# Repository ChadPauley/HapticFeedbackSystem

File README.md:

The purpose of this directory is to store PCB work and documentation on my first PCB design that was developed and sent to a fab house. While working on a team, I was tasked with designing the PCB layout for a Carrier Board that houses a CM4 module.
There are three versions of the PCB as we discovered issues and misleading information in the CM4 documentation such as camera pin layout. The final version worked and is in the primary CAD and schematic directory.

Version 2:
I2C lines for CAM1 are used for CAM0 which makes the camera a little finicky.

Version 3:
V3 fixes the issue with the camera and acts as a more ideal PCB.
--------------------------------------------------------------------------

After this project I have begun to focus more on the KiCAD software to design PCB fabs as a hobby due to the limitations of EAGLE only allowing 2 layers for the free version.

--------------------------------------------------------------------------
Real Fab Shape/Size:

--------------------------------------------------------------------------
CAD Layout:

--------------------------------------------------------------------------
Net paths:

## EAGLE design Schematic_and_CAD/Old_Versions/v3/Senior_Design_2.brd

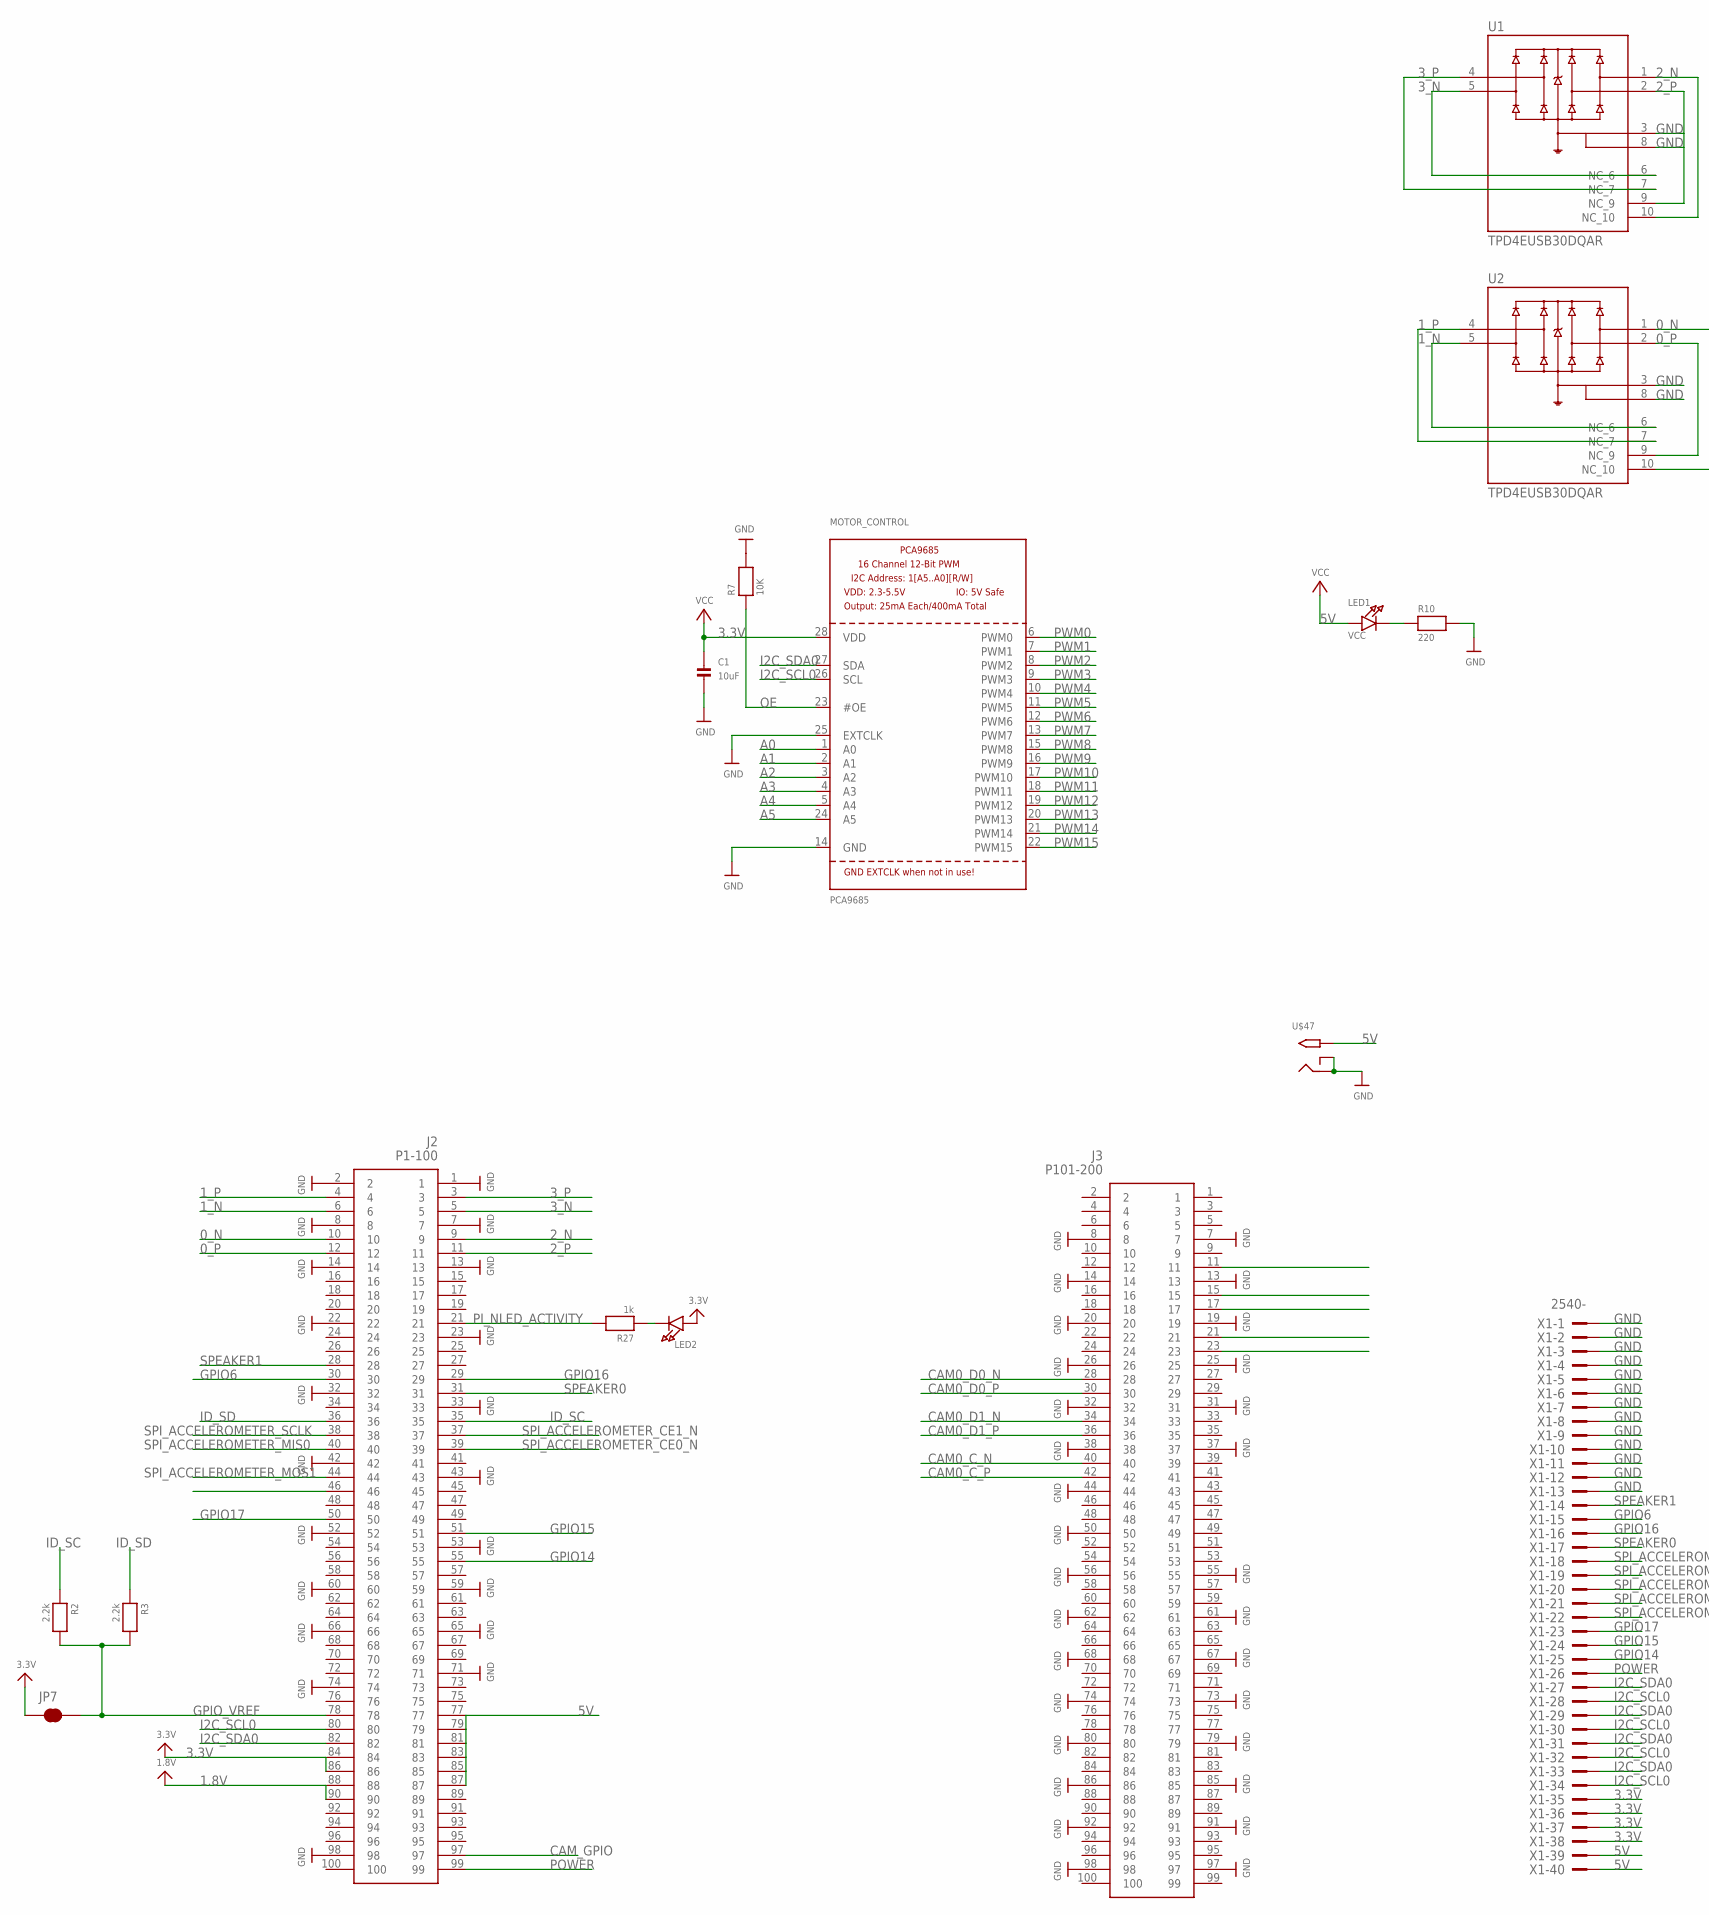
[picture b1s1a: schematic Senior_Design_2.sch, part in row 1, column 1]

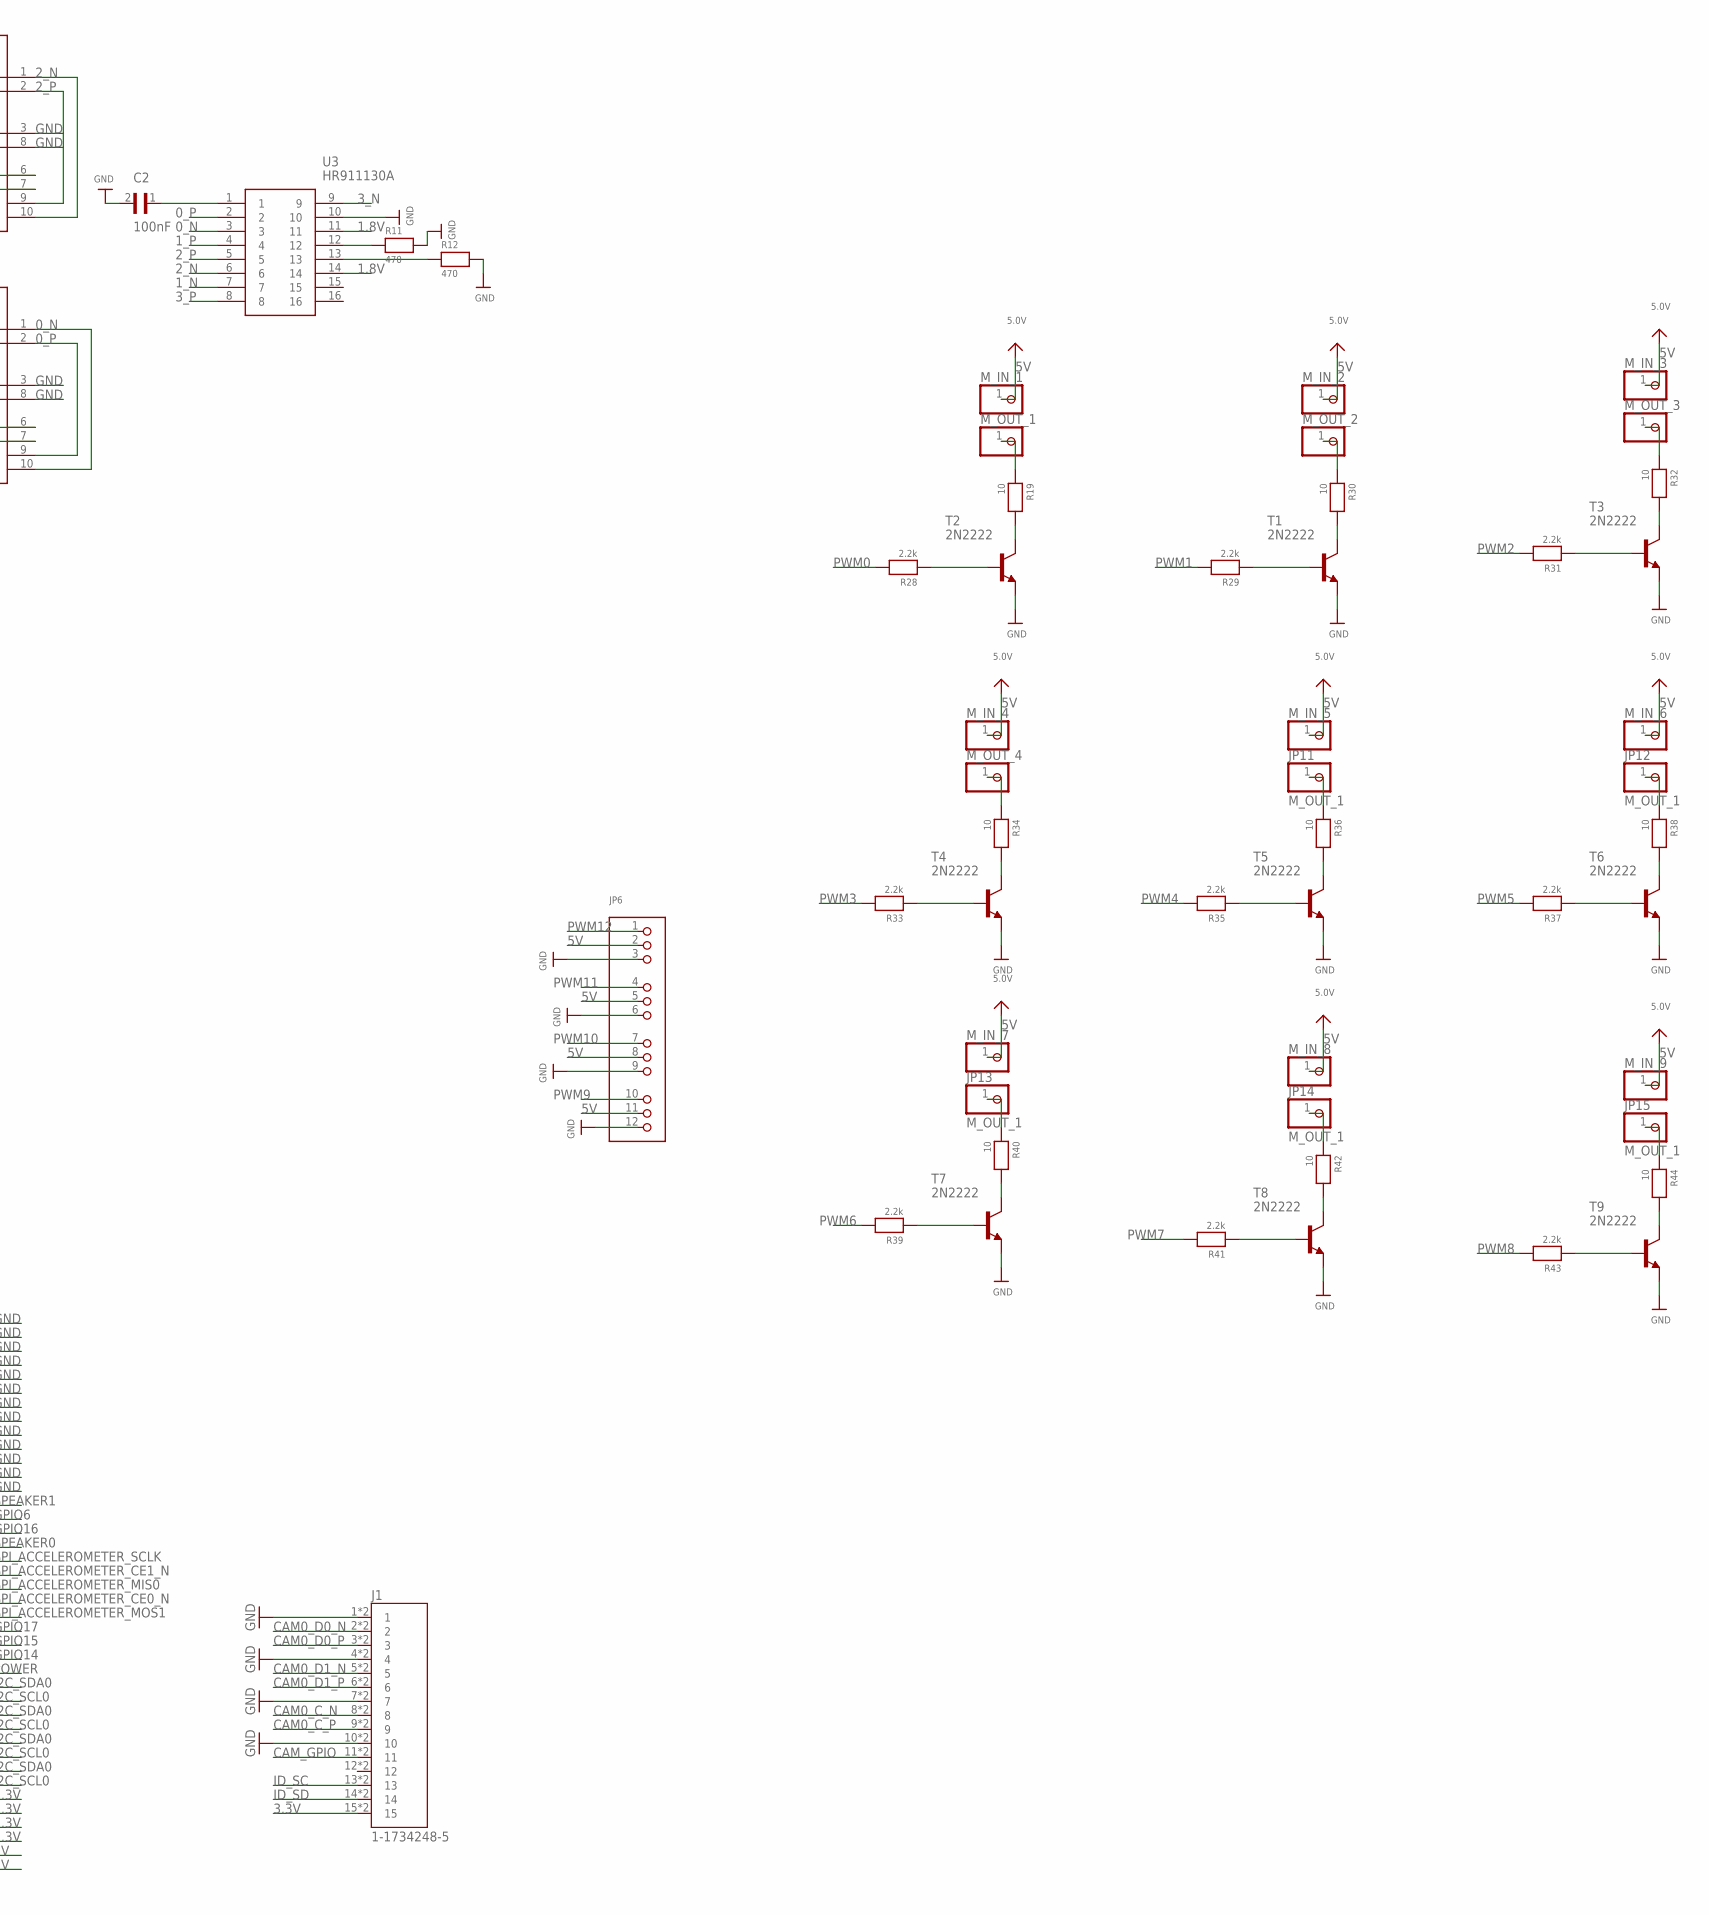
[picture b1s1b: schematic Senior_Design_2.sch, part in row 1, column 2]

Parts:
C1: 10uF; 0805@1
C2: 100nF; CAPC1608X90
J1: 1-1734248-5; TE_1-1734248-5
J2: P1-100; DF40C100DS04V51; MPN MCW0406MD1003BP100
J3: P101-200; DF40C100DS04V51
JP6: HEADER-3X04; 3X04
JP7: JUMPER-SMT_2_NC_TRACE_NO-SILK; SMT-JUMPER_2_NC_TRACE_NO-SILK
JP11, JP12, JP13, JP14, JP15: M_OUT_1; 1X01
LED1: VCC; CHIPLED_0805
LED2: LED0603; CHIPLED_0603; MPN LS Q976-NR-1
MOTOR_CONTROL: PCA9685; TSSOP28
M_IN_1, M_IN_2, M_IN_3, M_IN_4, M_IN_5, M_IN_6, M_IN_7, M_IN_8, M_IN_9: PINHD-1X1; 1X01
M_OUT_1, M_OUT_2, M_OUT_3, M_OUT_4: PINHD-1X1; 1X01
R2, R3, R28, R29, R31, R33, R35, R37, R39, R41, R43: 2.2k; 0805
R7: 10K; 0805
R10: 220; 0805
R11, R12: 470; 0805
R19, R30, R32, R34, R36, R38, R40, R42, R44: 10; 0805
R27: 1k; 0805
T1, T2, T3, T4, T5, T6, T7, T8, T9: 2N2222; TO92-EBC-OVAL
U1, U2: TPD4EUSB30DQAR; IC_TPD4EUSB30DQAR
U3: HR911130A
U$47: 2.1MMJACKTHM; PJ-102A
X1: 2540-; PAK100/2500-40

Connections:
0_N: J2.10, U2.1 (D1+), U2.10 (NC_10), U3.3
0_P: J2.12, U2.2 (D1-), U2.9 (NC_9), U3.2
1.8V: J2.88, J2.90, U3.11, U3.14
1_N: J2.6, U2.5 (D2-), U2.6 (NC_6), U3.7
1_P: J2.4, U2.4 (D2+), U2.7 (NC_7), U3.4
2_N: J2.9, U1.1 (D1+), U1.10 (NC_10), U3.6
2_P: J2.11, U1.2 (D1-), U1.9 (NC_9), U3.5
3.3V: C1.1, J1.15, J1.15_1 (15), J2.84, J2.86, JP7.1, LED2.A, MOTOR_CONTROL.28 (VDD), X1.35, X1.36, X1.37, X1.38
3_N: J2.5, U1.5 (D2-), U1.6 (NC_6), U3.9
3_P: J2.3, U1.4 (D2+), U1.7 (NC_7), U3.8
5V: J2.77, J2.79, J2.81, J2.83, J2.85, J2.87, JP6.2, JP6.5, JP6.8, JP6.11, LED1.A, M_IN_1.1, M_IN_2.1, M_IN_3.1, M_IN_4.1, M_IN_5.1, M_IN_6.1, M_IN_7.1, M_IN_8.1, M_IN_9.1, U$47.TIP, X1.39, X1.40
A0: MOTOR_CONTROL.1 (A0)
A1: MOTOR_CONTROL.2 (A1)
A2: MOTOR_CONTROL.3 (A2)
A3: MOTOR_CONTROL.4 (A3)
A4: MOTOR_CONTROL.5 (A4)
A5: MOTOR_CONTROL.24 (A5)
CAM0_C_N: J1.8, J1.8_1 (8), J3.40
CAM0_C_P: J1.9, J1.9_1 (9), J3.42
CAM0_D0_N: J1.2, J1.2_1 (2), J3.28
CAM0_D0_P: J1.3, J1.3_1 (3), J3.30
CAM0_D1_N: J1.5, J1.5_1 (5), J3.34
CAM0_D1_P: J1.6, J1.6_1 (6), J3.36
CAM_GPIO: J1.11, J1.11_1 (11), J2.97
GND: C1.2, C2.2, J1.1, J1.1_1 (1), J1.4, J1.4_1 (4), J1.7, J1.7_1 (7), J1.10, J1.10_1 (10), J2.1, J2.2, J2.7, J2.8, J2.13, J2.14, J2.22, J2.23, J2.32, J2.33, J2.42, J2.43, J2.52, J2.53, J2.59, J2.60, J2.65, J2.66, J2.71, J2.74, J2.98, J3.7, J3.8, J3.13, J3.14, J3.19, J3.20, J3.25, J3.26, J3.31, J3.32, J3.37, J3.38, J3.44, J3.50, J3.55, J3.56, J3.61, J3.62, J3.67, J3.68, J3.73, J3.74, J3.79, J3.80, J3.85, J3.86, J3.91, J3.92, J3.97, J3.98, JP6.3, JP6.6, JP6.9, JP6.12, MOTOR_CONTROL.14 (GND), MOTOR_CONTROL.25 (EXTCLK), R7.2, R10.2, R11.2, R12.2, T1.E, T2.E, T3.E, T4.E, T5.E, T6.E, T7.E, T8.E, T9.E, U1.3 (GND_3), U1.8 (GND_8), U2.3 (GND_3), U2.8 (GND_8), U3.10, U$47.RING, U$47.RING_SW, X1.1, X1.2, X1.3, X1.4, X1.5, X1.6, X1.7, X1.8, X1.9, X1.10, X1.11, X1.12, X1.13
GPIO6: J2.30, X1.15
GPIO14: J2.55, X1.25
GPIO15: J2.51, X1.24
GPIO16: J2.29, X1.16
GPIO17: J2.50, X1.23
GPIO_VREF: J2.78, JP7.2, R2.2, R3.2
I2C_SCL0: J2.80, MOTOR_CONTROL.26 (SCL), X1.28, X1.30, X1.32, X1.34
I2C_SDA0: J2.82, MOTOR_CONTROL.27 (SDA), X1.27, X1.29, X1.31, X1.33
ID_SC: J1.13, J1.13_1 (13), J2.35, R2.1
ID_SD: J1.14, J1.14_1 (14), J2.36, R3.1
unnamed: LED1.C, R10.1
unnamed: C2.1, U3.1
unnamed: R11.1, U3.12
unnamed: R12.1, U3.13
unnamed: R19.2, T2.C
unnamed: LED2.C, R27.1
unnamed: R28.1, T2.B
unnamed: M_OUT_1.1, R19.1
unnamed: R29.1, T1.B
unnamed: R30.2, T1.C
unnamed: M_OUT_2.1, R30.1
unnamed: R31.1, T3.B
unnamed: R32.2, T3.C
unnamed: M_OUT_3.1, R32.1
unnamed: R33.1, T4.B
unnamed: R34.2, T4.C
unnamed: M_OUT_4.1, R34.1
unnamed: R35.1, T5.B
unnamed: R36.2, T5.C
unnamed: JP11.1, R36.1
unnamed: R37.1, T6.B
unnamed: R38.2, T6.C
unnamed: JP12.1, R38.1
unnamed: R39.1, T7.B
unnamed: R40.2, T7.C
unnamed: JP13.1, R40.1
unnamed: R41.1, T8.B
unnamed: R42.2, T8.C
unnamed: JP14.1, R42.1
unnamed: R43.1, T9.B
unnamed: R44.2, T9.C
unnamed: JP15.1, R44.1
OE: MOTOR_CONTROL.23 (#OE), R7.1
PI_NLED_ACTIVITY: J2.21, R27.2
POWER: J2.99, X1.26
PWM0: MOTOR_CONTROL.6 (PWM0), R28.2
PWM1: MOTOR_CONTROL.7 (PWM1), R29.2
PWM2: MOTOR_CONTROL.8 (PWM2), R31.2
PWM3: MOTOR_CONTROL.9 (PWM3), R33.2
PWM4: MOTOR_CONTROL.10 (PWM4), R35.2
PWM5: MOTOR_CONTROL.11 (PWM5), R37.2
PWM6: MOTOR_CONTROL.12 (PWM6), R39.2
PWM7: MOTOR_CONTROL.13 (PWM7), R41.2
PWM8: MOTOR_CONTROL.15 (PWM8), R43.2
PWM9: JP6.10, MOTOR_CONTROL.16 (PWM9)
PWM10: JP6.7, MOTOR_CONTROL.17 (PWM10)
PWM11: JP6.4, MOTOR_CONTROL.18 (PWM11)
PWM12: JP6.1, MOTOR_CONTROL.19 (PWM12)
PWM13: MOTOR_CONTROL.20 (PWM13)
PWM14: MOTOR_CONTROL.21 (PWM14)
PWM15: MOTOR_CONTROL.22 (PWM15)
SPEAKER0: J2.31, X1.17
SPEAKER1: J2.28, X1.14
SPI_ACCELEROMETER_CE0_N: J2.39, X1.21
SPI_ACCELEROMETER_CE1_N: J2.37, X1.19
SPI_ACCELEROMETER_MIS0: J2.40, X1.20
SPI_ACCELEROMETER_MOS1: J2.44, X1.22
SPI_ACCELEROMETER_SCLK: J2.38, X1.18

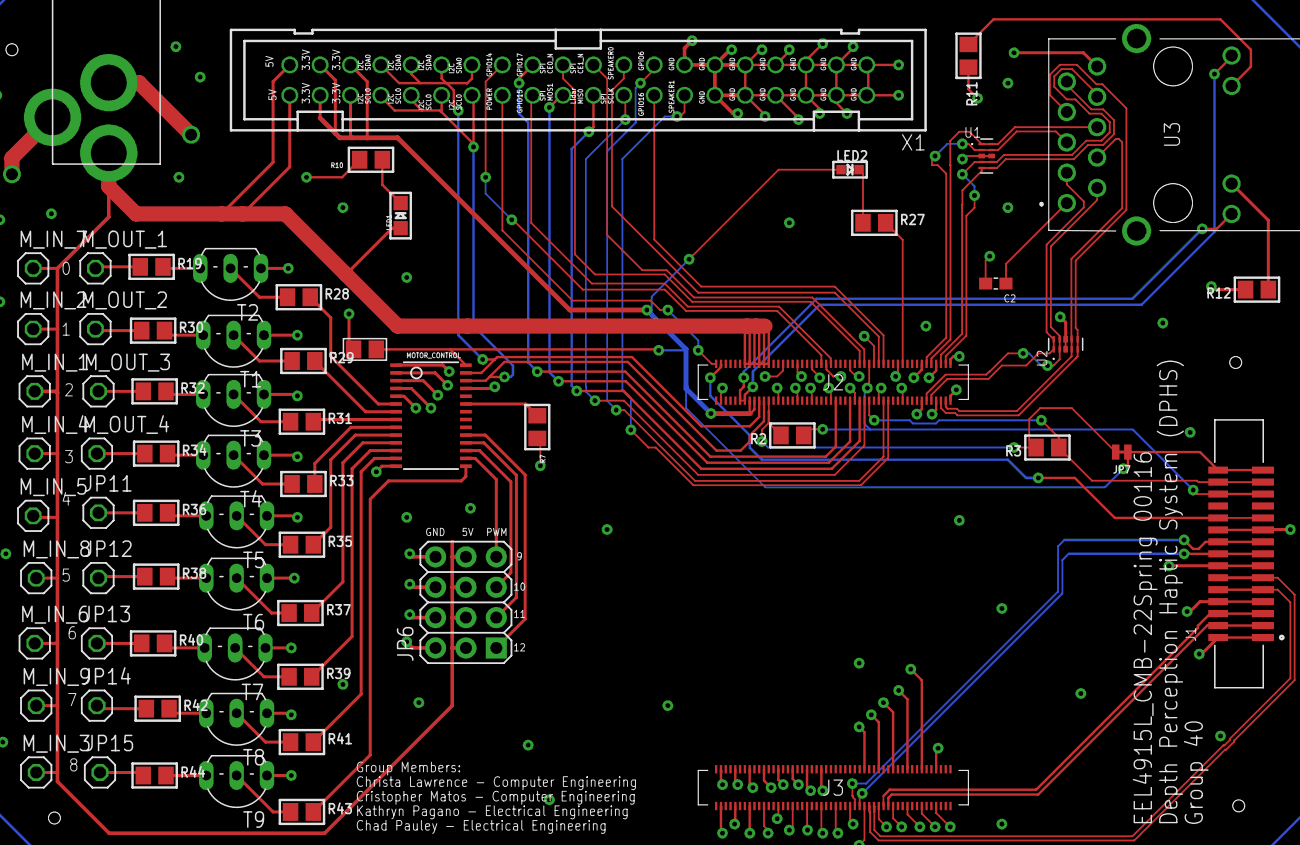
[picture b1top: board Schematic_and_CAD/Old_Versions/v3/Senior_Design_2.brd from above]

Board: 2 copper layers, 67 parts (0 on the bottom side), 84 nets.

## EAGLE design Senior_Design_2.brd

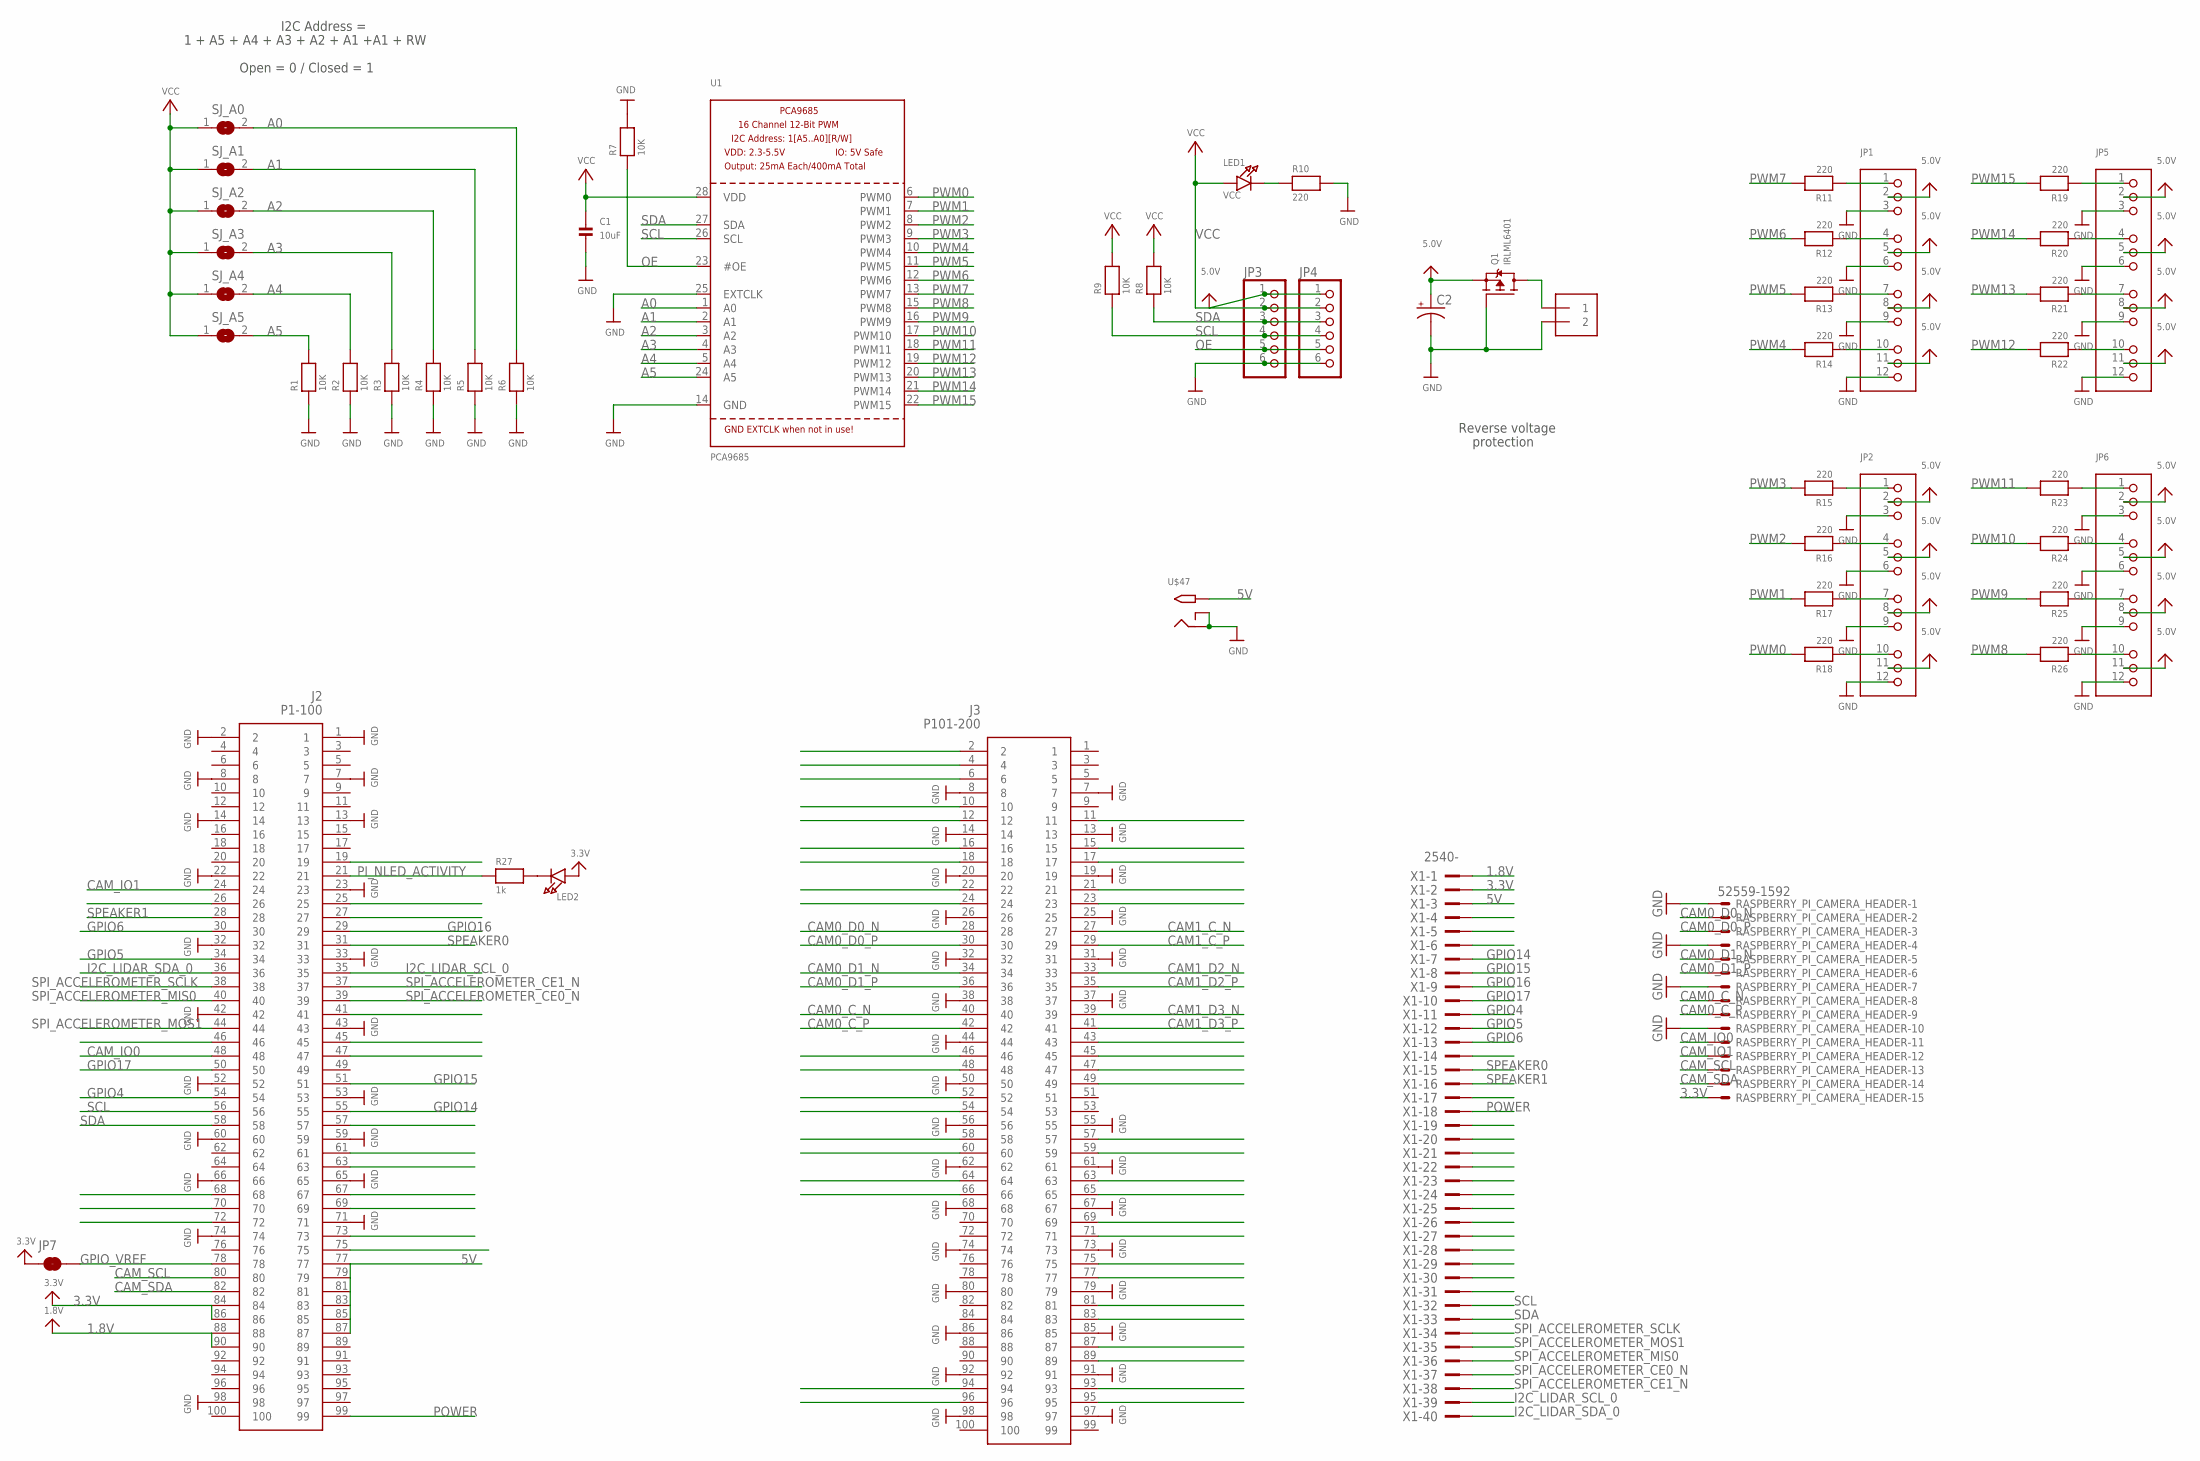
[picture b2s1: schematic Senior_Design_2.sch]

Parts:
C1: 10uF; 0805@1
C2: CPOL-USE3.5-8; E3,5-8
J1: TERMBLOCK_1X2-3.5MM; 1X2-3.5MM
J2: P1-100; DF40C100DS04V51; MPN MCW0406MD1003BP100
J3: P101-200; DF40C100DS04V51
JP1, JP2, JP5, JP6: HEADER-3X04; 3X04
JP3, JP4: PINHD-1X6CB; 1X06-CLEANBIG
JP7: JUMPER-SMT_2_NC_TRACE_NO-SILK; SMT-JUMPER_2_NC_TRACE_NO-SILK
LED1: VCC; CHIPLED_0805
LED2: LED0603; CHIPLED_0603; MPN LS Q976-NR-1
Q1: IRLML6401; SOT23-WIDE
R1, R2, R3, R4, R5, R6, R7, R8, R9: 10K; 0805
R10, R11, R12, R13, R14, R15, R16, R17, R18, R19, R20, R21, R22, R23, R24, R25, R26: 220; 0805
R27: 1k; _0402MP; MPN ERJ-8ENF1001V
RASPBERRY_PI_CAMERA_HEADER: 52559-1592
SJ_A0, SJ_A1, SJ_A2, SJ_A3, SJ_A4, SJ_A5: SOLDERJUMPERREFLOW_NOPASTE; SOLDERJUMPER_REFLOW_NOPASTE
U1: PCA9685; TSSOP28
U$47: 2.1MMJACKTHM; PJ-102A
X1: 2540-; PAK100/2500-40

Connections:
1.8V: J2.88, J2.90, X1.1
3.3V: J2.84, J2.86, JP7.1, LED2.A, RASPBERRY_PI_CAMERA_HEADER.15, X1.2
5.0V: C2.+, JP1.2, JP1.5, JP1.8, JP1.11, JP2.2, JP2.5, JP2.8, JP2.11, JP3.1, JP4.1, JP5.2, JP5.5, JP5.8, JP5.11, JP6.2, JP6.5, JP6.8, JP6.11, Q1.2 (S)
5V: J2.77, J2.79, J2.81, J2.83, J2.85, J2.87, U$47.TIP, X1.3
A0: R6.2, SJ_A0.2, U1.1 (A0)
A1: R5.2, SJ_A1.2, U1.2 (A1)
A2: R4.2, SJ_A2.2, U1.3 (A2)
A3: R3.2, SJ_A3.2, U1.4 (A3)
A4: R2.2, SJ_A4.2, U1.5 (A4)
A5: R1.2, SJ_A5.2, U1.24 (A5)
CAM0_C_N: J3.40, RASPBERRY_PI_CAMERA_HEADER.8
CAM0_C_P: J3.42, RASPBERRY_PI_CAMERA_HEADER.9
CAM0_D0_N: J3.28, RASPBERRY_PI_CAMERA_HEADER.2
CAM0_D0_P: J3.30, RASPBERRY_PI_CAMERA_HEADER.3
CAM0_D1_N: J3.34, RASPBERRY_PI_CAMERA_HEADER.5
CAM0_D1_P: J3.36, RASPBERRY_PI_CAMERA_HEADER.6
CAM1_C_N: J3.27
CAM1_C_P: J3.29
CAM1_D2_N: J3.33
CAM1_D2_P: J3.35
CAM1_D3_N: J3.39
CAM1_D3_P: J3.41
CAM_IO0: J2.48, RASPBERRY_PI_CAMERA_HEADER.11
CAM_IO1: J2.24, RASPBERRY_PI_CAMERA_HEADER.12
CAM_SCL: J2.80, RASPBERRY_PI_CAMERA_HEADER.13
CAM_SDA: J2.82, RASPBERRY_PI_CAMERA_HEADER.14
GND: C1.2, C2.-, J1.2, J2.1, J2.2, J2.7, J2.8, J2.13, J2.14, J2.22, J2.23, J2.32, J2.33, J2.42, J2.43, J2.52, J2.53, J2.59, J2.60, J2.65, J2.66, J2.71, J2.74, J2.98, J3.7, J3.8, J3.13, J3.14, J3.19, J3.20, J3.25, J3.26, J3.31, J3.32, J3.37, J3.38, J3.44, J3.50, J3.55, J3.56, J3.61, J3.62, J3.67, J3.68, J3.73, J3.74, J3.79, J3.80, J3.85, J3.86, J3.91, J3.92, J3.97, J3.98, JP1.3, JP1.6, JP1.9, JP1.12, JP2.3, JP2.6, JP2.9, JP2.12, JP3.6, JP4.6, JP5.3, JP5.6, JP5.9, JP5.12, JP6.3, JP6.6, JP6.9, JP6.12, Q1.1 (G), R1.1, R2.1, R3.1, R4.1, R5.1, R6.1, R7.2, R10.2, RASPBERRY_PI_CAMERA_HEADER.1, RASPBERRY_PI_CAMERA_HEADER.4, RASPBERRY_PI_CAMERA_HEADER.7, RASPBERRY_PI_CAMERA_HEADER.10, U1.14 (GND), U1.25 (EXTCLK), U$47.RING, U$47.RING_SW
GPIO4: J2.54, X1.11
GPIO5: J2.34, X1.12
GPIO6: J2.30, X1.13
GPIO14: J2.55, X1.7
GPIO15: J2.51, X1.8
GPIO16: J2.29, X1.9
GPIO17: J2.50, X1.10
GPIO_VREF: J2.78, JP7.2
I2C_LIDAR_SCL_0: J2.35, X1.39
I2C_LIDAR_SDA_0: J2.36, X1.40
unnamed: LED1.C, R10.1
unnamed: JP1.4, R12.1
unnamed: JP1.1, R11.1
unnamed: JP1.7, R13.1
unnamed: JP1.10, R14.1
unnamed: JP2.1, R15.1
unnamed: JP2.4, R16.1
unnamed: JP2.7, R17.1
unnamed: JP2.10, R18.1
unnamed: JP6.10, R26.1
unnamed: JP6.7, R25.1
unnamed: JP6.4, R24.1
unnamed: JP6.1, R23.1
unnamed: JP5.10, R22.1
unnamed: JP5.7, R21.1
unnamed: JP5.4, R20.1
unnamed: JP5.1, R19.1
unnamed: LED2.C, R27.2
OE: JP3.5, JP4.5, R7.1, U1.23 (#OE)
PI_NLED_ACTIVITY: J2.21, R27.1
POWER: J2.99, X1.18
PWM0: R18.2, U1.6 (PWM0)
PWM1: R17.2, U1.7 (PWM1)
PWM2: R16.2, U1.8 (PWM2)
PWM3: R15.2, U1.9 (PWM3)
PWM4: R14.2, U1.10 (PWM4)
PWM5: R13.2, U1.11 (PWM5)
PWM6: R12.2, U1.12 (PWM6)
PWM7: R11.2, U1.13 (PWM7)
PWM8: R26.2, U1.15 (PWM8)
PWM9: R25.2, U1.16 (PWM9)
PWM10: R24.2, U1.17 (PWM10)
PWM11: R23.2, U1.18 (PWM11)
PWM12: R22.2, U1.19 (PWM12)
PWM13: R21.2, U1.20 (PWM13)
PWM14: R20.2, U1.21 (PWM14)
PWM15: R19.2, U1.22 (PWM15)
PWRIN: J1.1, Q1.3 (D)
SCL: J2.56, JP3.4, JP4.4, R9.1, U1.26 (SCL), X1.32
SDA: J2.58, JP3.3, JP4.3, R8.1, U1.27 (SDA), X1.33
SPEAKER0: J2.31, X1.15
SPEAKER1: J2.28, X1.16
SPI_ACCELEROMETER_CE0_N: J2.39, X1.37
SPI_ACCELEROMETER_CE1_N: J2.37, X1.38
SPI_ACCELEROMETER_MIS0: J2.40, X1.36
SPI_ACCELEROMETER_MOS1: J2.44, X1.35
SPI_ACCELEROMETER_SCLK: J2.38, X1.34
VCC: C1.1, JP3.2, JP4.2, LED1.A, R8.2, R9.2, SJ_A0.1, SJ_A1.1, SJ_A2.1, SJ_A3.1, SJ_A4.1, SJ_A5.1, U1.28 (VDD)

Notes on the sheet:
Reverse voltage
protection
1 + A5 + A4 + A3 + A2 + A1 +A1 + RW
I2C Address =
Open = 0 / Closed = 1

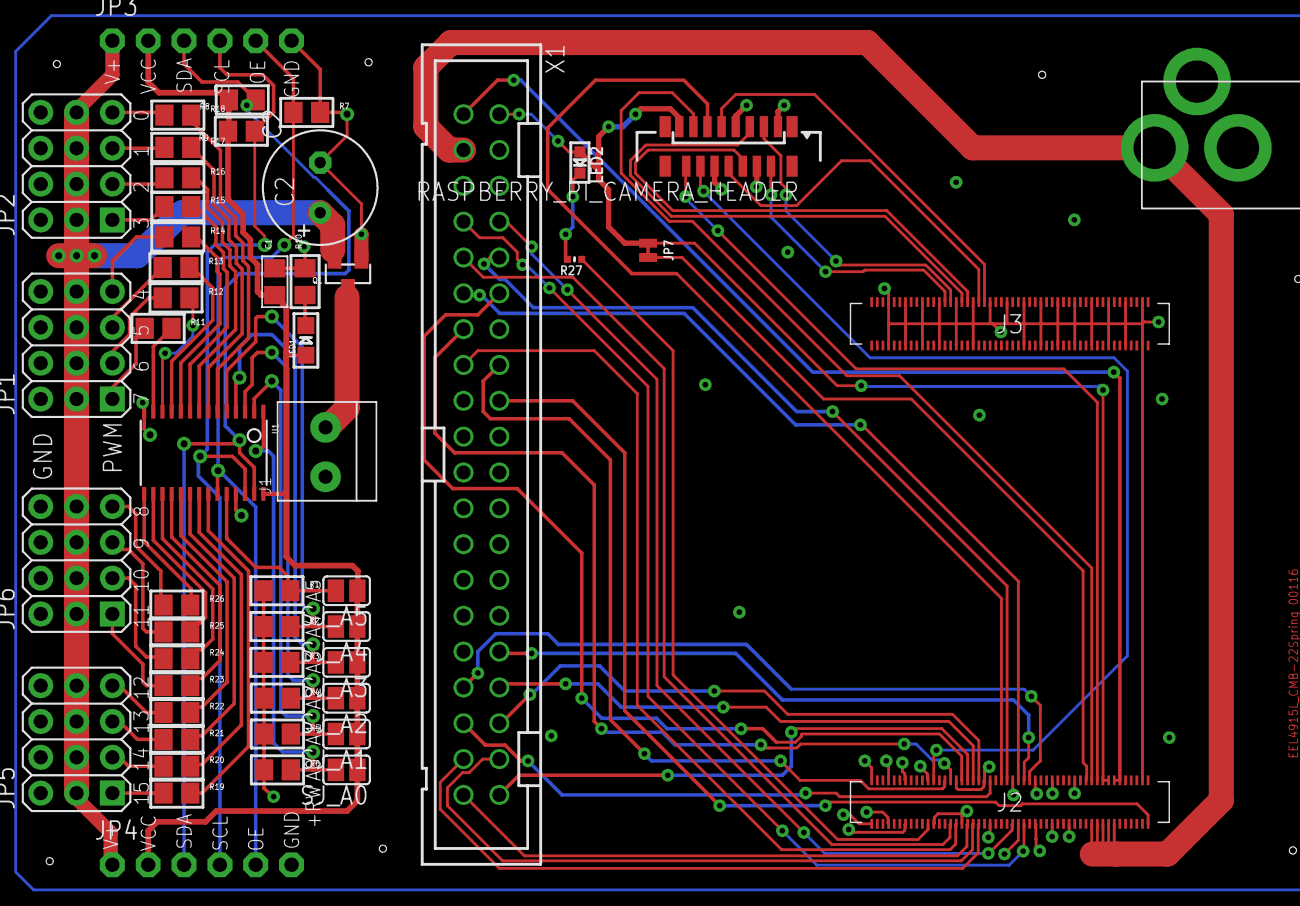
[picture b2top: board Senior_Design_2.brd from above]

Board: 2 copper layers, 52 parts (0 on the bottom side), 79 nets.

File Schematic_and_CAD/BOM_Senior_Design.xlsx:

BOM for Senior_Design PCB
Description: This PCB is intended to act as a carryout board (like a motherboar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
Item # | Ref Des | Qty | Stock | Manufacturer | Mfg Part # | Description/Value | Website
1 | R1N R2, R3, R4, R5, R6, R8, R9 | 8 | 4556 | TE Connectivity Passive Product | 352210KJT | 10k Resistors | https://www.digikey.com/en/products/detail/te-connectivity-p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
2 | PCA9685 | 1 | 474 | NXP Semiconductors | PCA9685PW,118 | 16 Channel 12-Bit PWM | https://www.mouser.com/ProductDetail/NXP-Semiconductors/PCA9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
3 | LED1, LED2 | 2 | 92453 | American Opto Plus LED | L513GD-B | Green LED | https://www.digikey.com/en/products/detail/american-opto-plu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
4 | R10, R11, R12, R13, R14, R15, R16, R17, R18, R19, R20, R21, R22, R23, R24, R25,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 | 17 | 328 | TE Connectivity Passive Product | 3522220RJT | 220 ohm Resistor | https://www.digikey.co.uk/en/products/detail/te-connectivity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
5 | C2 | 1 | N/A | N/A | N/A | Capacitor of about 600 uF. Ignore this part as the device still functions witho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
6 | Q1 | 1 | Unknown | Infineon | IRLML6401 | IRLML6401, voltage protection | https://www.mouser.com/ProductDetail/Infineon-IR/IRLML6401?q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
7 | U$47 | 1 | 91289 | CUI Devices | PJ-102A | Power Jack | https://www.digikey.com/en/products/detail/cui-devices/PJ-10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
8 | R27 | 1 | 4531809 | YAGEO | RC0805FR-071KL | 1K resistor | https://www.digikey.com/en/products/detail/yageo/RC0805FR-07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
9 | 2540- | 1 | 4606240 | THD | THD-20-R | 40 pin (20x2) pin header, male | https://www.toby.co.uk/board-to-board-pcb-connectors/254mm-h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
10 | 52559-1592 | 1 | 310 | Molex | 52271-1579 | Raspberry Pi Camera Header (15 pin) | https://sg.rs-online.com/web/p/fpc-connectors/6706827
11 | J2+, J3+ | 2 | 11020 | Hirose Electric Co Ltd | DF40C-100DS-0.4V(51) | CONN RCPT 100POS 0.4MM SMD GOLD | https://www.integrated-circuit.com/products-detail/DF40C-100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
Minor modification to the circuit will be needed if item #6 cannot be obtained.

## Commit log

2024-10-05 BOM, Schematic, and CAD files.
2024-10-05 Footprints
    The footprints used in the CAD Design
2024-10-05 Rename Footprints to Footprint_Library/Footprint
2024-10-05 Rename BOM_Senior_Design.xlsx to Schematic_and_CAD/BOM_Senior_Design.xlsx
2024-10-05 Footprint Files
    May be missing some items required for brd file, discretion is advised.
2024-10-05 Deleting temp
2024-10-05 Rename Senior_Design_2.brd to Schematic_and_CAD/Schematic_and_CADSenior_Design_2.brd
2024-10-05 Rename Senior_Design_2.sch to Schematic_and_CAD/Senior_Design_2.sch
2024-10-05 Rename Senior_Design_2_EAGLE.zip to Schematic_and_CAD/Senior_Design_2_EAGLE.zip
2024-10-05 Rename Senior_Design_GERBER.zip to Schematic_and_CAD/Senior_Design_GERBER.zip
2024-10-05 Create temp
2024-10-05 2022 UCF Senior Design Documentation
2024-10-05 Development images
2024-10-05 Eagle Library
    All footprints used in development. Some files may not be used or have been modified from the source. Use at own risk.
2024-10-05 Rotating image

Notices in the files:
parts and their libraries:
SparkFun-Jumpers: Licensing: Creative Commons ShareAlike 4.0 International - https://creativecommons.org/licenses/by-sa/4.0
